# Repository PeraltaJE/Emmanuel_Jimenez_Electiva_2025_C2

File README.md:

ESTAS SON LAS TAREAS Y DISEÑOS DE LA ELECTIVA DE MECATRONICA

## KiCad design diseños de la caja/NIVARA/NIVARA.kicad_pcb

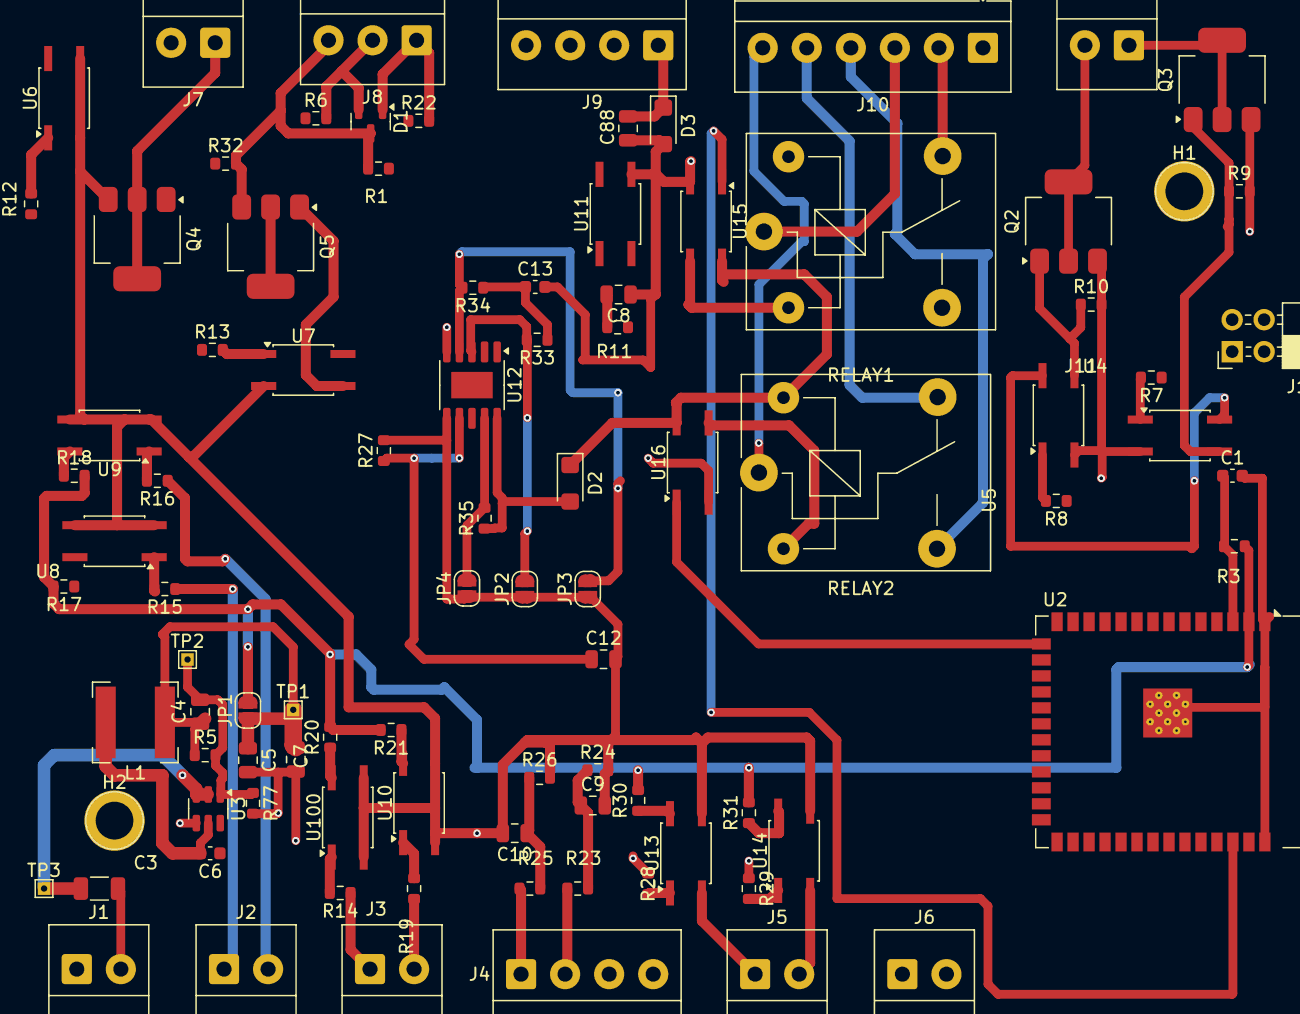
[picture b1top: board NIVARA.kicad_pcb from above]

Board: 4 copper layers, 93 parts (0 on the bottom side), 61 nets.

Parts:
C1: 1uf; C_0603_1608Metric
C3: 10mf; C_1206_3216Metric
C4: 100nf; C_0805_2012Metric
C5, C7: 22uf; C_0805_2012Metric
C6: 100nf; C_0603_1608Metric
C8: 1uF; C_0805_2012Metric
C9, C10, C88: 100nF; C_0805_2012Metric
C12: 220pF; C_0805_2012Metric
C13: 1uF; C_0603_1608Metric
D1: SM712_SOT23; SOT-23
D2: D_Zener; D_SMF
D3: SMF24A; D_SMF
H1, H2: MountingHole; TestPoint_Plated_Hole_D3.0mm
J1, J2, J3, J5, J6, J7, J11: Screw_Terminal_01x02; TerminalBlock_4Ucon_1x02_P3.50mm_Horizontal
J4, J9: Screw_Terminal_01x04; TerminalBlock_4Ucon_1x04_P3.50mm_Horizontal
J8: Screw_Terminal_01x03; TerminalBlock_4Ucon_1x03_P3.50mm_Horizontal
J10: Screw_Terminal_01x06; TerminalBlock_4Ucon_1x06_P3.50mm_Horizontal
J12: USB_ext; PinSocket_2x02_P2.54mm_Horizontal
JP1, JP2, JP3, JP4: SolderJumper_2_Open; SolderJumper-2_P1.3mm_Open_RoundedPad1.0x1.5mm
L1: L_Iron; L_Bourns-SRN6028
Q2, Q3, Q4, Q5: NCV8402xST; SOT-223
R1, R3, R5, R6, R22, R77: R_US; R_0603_1608Metric
R7, R8, R12, R13: 100; R_0603_1608Metric
R9, R10, R32: R; R_0603_1608Metric
R11, R33, R34, R35: 10k; R_0603_1608Metric
R14, R15, R16, R19, R28, R29: 910; R_0603_1608Metric
R17, R18, R20, R21, R30, R31: 412; R_0603_1608Metric
R23: 160k; R_0603_1608Metric
R24: 13k; R_0603_1608Metric
R25: 51k; R_0603_1608Metric
R26: 16k; R_0603_1608Metric
R27: 2.5k; R_0603_1608Metric
RELAY1, RELAY2: SANYOU_SRD_Form_C; Relay_SPDT_SANYOU_SRD_Series_Form_C
TP1, TP2, TP3: TestPoint; TestPoint_THTPad_1.0x1.0mm_Drill0.5mm
U2: ESP32-S3-WROOM-1
U3: AP63203WU; TSOT-23-6
U4, U5, U6, U7: LTV-357T; SO-4_4.4x3.6mm_P2.54mm
U8, U9, U10, U11, U13, U14, U15, U16, U100: LTV-357TB; SO-4_4.4x3.6mm_P2.54mm
U12: SSOP-10-1EP_3.9x4.9mm_P1mm_EP2.1x3.3mm

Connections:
+3.3V: JP1.2 (B), R3.1, R17.2, R18.2, R20.2, R21.2, R30.2, R31.2, U2.2 (3V3)
/NIVARA_ZORIONX_BOARD/10V_AIN/10V_ADC: C10.1, R25.2, R26.1
/NIVARA_ZORIONX_BOARD/32V_AIN/32V_ADC: C9.1, R23.2, R24.1
/NIVARA_ZORIONX_BOARD/+10V_AINPUT: J4.1, R25.1
/NIVARA_ZORIONX_BOARD/+32V_AINPUT: J4.2, R23.1
/NIVARA_ZORIONX_BOARD/DRY_DINPUT_0: J5.1, U13.2
/NIVARA_ZORIONX_BOARD/DRY_DINPUT_1: J5.2, U14.2
/NIVARA_ZORIONX_BOARD/DRY_INPUT/DRY_OUT0: R30.1, U13.4
/NIVARA_ZORIONX_BOARD/DRY_INPUT/DRY_OUT1: R31.1, U14.4
/NIVARA_ZORIONX_BOARD/NPN_DINPUT_0: J2.1, R15.1
/NIVARA_ZORIONX_BOARD/NPN_DINPUT_1: J2.2, R16.1
/NIVARA_ZORIONX_BOARD/NPN_DOUTPUT_0: J11.1, Q3.2 (D), Q3.4 (D)
/NIVARA_ZORIONX_BOARD/NPN_DOUTPUT_1: J11.2, Q2.2 (D), Q2.4 (D)
/NIVARA_ZORIONX_BOARD/NPN_IN/NPN_Output0: R17.1, U8.4
/NIVARA_ZORIONX_BOARD/NPN_IN/NPN_Output1: R18.1, U9.4
/NIVARA_ZORIONX_BOARD/PNP_DINPUT_0: J3.1, R14.1
/NIVARA_ZORIONX_BOARD/PNP_DINPUT_1: J3.2, R19.1
/NIVARA_ZORIONX_BOARD/PNP_DOUTPUT_0: J7.1, Q4.2 (D), Q4.4 (D)
/NIVARA_ZORIONX_BOARD/PNP_DOUTPUT_1: Q5.2 (D), Q5.4 (D)
/NIVARA_ZORIONX_BOARD/PNP_IN/PNP_Output0: R20.1, U100.4
/NIVARA_ZORIONX_BOARD/PNP_IN/PNP_Output1: R21.1, U10.4
/NIVARA_ZORIONX_BOARD/POWER SUPPLY/30v: C3.1, TP3.1, U3.2 (EN), U3.3 (IN)
/NIVARA_ZORIONX_BOARD/POWER SUPPLY/SW: C6.2, L1.1, U3.5 (SW)
/NIVARA_ZORIONX_BOARD/POWER SUPPLY/Vout: C4.1, C5.1, C7.1, JP1.1 (A), L1.2, R5.1, TP1.1
/NIVARA_ZORIONX_BOARD/RELAY/RL1_EN: U2.38 (GPIO2/TOUCH2/ADC1_CH1), U15.1
/NIVARA_ZORIONX_BOARD/RELAY/RL2_EN: U2.15 (GPIO3/TOUCH3/ADC1_CH2), U16.1
/NIVARA_ZORIONX_BOARD/RL1_COM: J10.3, RELAY1.1
/NIVARA_ZORIONX_BOARD/RL1_OUTPUT_NC: J10.2, RELAY1.4
/NIVARA_ZORIONX_BOARD/RL2_COM: J10.6, RELAY2.1
/NIVARA_ZORIONX_BOARD/RL2_OUTPUT_NC: J10.5, RELAY2.4
/NIVARA_ZORIONX_BOARD/RL2_OUTPUT_NO: J10.4, RELAY2.3
/NIVARA_ZORIONX_BOARD/RS485_A: D1.1 (A1), J8.1, R22.2
/NIVARA_ZORIONX_BOARD/RS485_B: D1.2 (A2), J8.2, R6.2
/NIVARA_ZORIONX_BOARD/VOLTAGE_AOUTPUT: C88.2, D3.1 (A1), J9.1
GND: C1.2, C3.2, C5.2, C7.2, C8.1, C9.2, C10.2, C12.2, C13.2, C88.1, D1.3 (common), D3.2 (A2), J1.2, J4.4, J6.2, J8.3, J9.4, JP2.1 (A), JP3.1 (A), JP4.1 (A), Q2.3 (S), Q3.3 (S), Q4.3 (S), Q5.3 (S), R1.2, R9.2, R10.2, R24.2, R26.2, R27.2, R32.2, R77.2, U2.1 (GND), U2.40 (GND), U2.41 (GND), U3.4 (GND), U4.2, U5.2, U6.2, U6.3, U7.2, U8.2, U8.3, U9.2, U9.3, U10.2, U10.3, U11.3, U12.6 (GND), U13.3, U14.3, U15.2, U16.2, U100.2, U100.3
NPN_VCC: U4.4, U5.4
unnamed: C13.1, D2.2 (A), R33.1, R34.1, R35.1, U12.10 (V5V)
unnamed: RELAY1.2, U15.3
unnamed: RELAY2.2, U16.3
unnamed: JP2.2 (B), R33.2, U12.3 (A0)
unnamed: JP3.2 (B), R34.2, U12.4 (A1)
unnamed: JP4.2 (B), R35.2, U12.9 (A2)
unnamed: Q2.1 (G), R10.1, U5.3
unnamed: Q3.1 (G), R9.1, U4.3
unnamed: Q5.1 (G), R32.1, U7.3
unnamed: R7.2, U4.1
unnamed: R8.2, U5.1
unnamed: R12.2, U6.1
unnamed: R13.2, U7.1
unnamed: R14.2, U100.1
unnamed: R15.2, U8.1
unnamed: R16.2, U9.1
unnamed: R19.2, U10.1
unnamed: R28.2, U13.1
unnamed: R29.2, U14.1
unnamed: C1.1, R3.2, U2.3 (EN)
unnamed: C6.1, U3.6 (BST)
unnamed: C4.2, R5.2, R77.1, TP2.1, U3.1 (FB)
unnamed: C8.2, R11.2
unnamed: C12.1, R27.1, U12.7 (SET)
VCC: D2.1 (K), J1.1, R28.1, R29.1, RELAY1.5, RELAY2.5, U12.5 (VCC), U15.4, U16.4

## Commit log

2025-05-22 Create REQUISITOS
2025-05-22 Create fotos
2025-05-22 Update fotos
2025-06-05 Create INVESTIGACION tarea 3
2025-06-05 Update INVESTIGACION tarea 3
2025-06-05 INVESTIGACION tarea 3
2025-06-05 Rename INVESTIGACION tarea 3 to Tarea 3/INVESTIGACION tarea 3
